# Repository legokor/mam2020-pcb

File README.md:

## Pinout

### LoRa
| Pin | ESP GPIO |
| ------ | ------ |
| MISO (2) | 19 |
| MOSI (3) | 23 |
| CLK (4) | 18 |
| CS (5)| 5 |
| RST (6)| 22 |
| DI0 (14) | 21 |

### Motors
| Pin | ESP GPIO |
| ------ | ------ |
| MOTOR_1_STEP | 27 |
| MOTOR_1_DIR | 14 |
| MOTOR_2_STEP | 12 |
| MOTOR_2_DIR | 17 |
| MOTOR_MODE_0 | 16 |
| MOTOR_MODE_1 | 4 |
| MOTOR_MODE_2 | 0 |

### ADC
| Pin | ESP GPIO |
| ------ | ------ |
| BATTERY | 34 |

### Servos
| Pin | ESP GPIO |
| ------ | ------ |
| SERVO_1 | 25 |
| SERVO_2 | 26 |

### Leds
| Pin | ESP GPIO |
| ------ | ------ |
| LED_1 | 35 |
| LED_2 | 32 |
| LED_3 | 33 |

### Connector

## Parts list

| Name | Link |
| ------ | ------ |
| ESP32 | [Pinout](https://www.rpibolt.hu/img/15922/RPI-WS16611_altpic_4/RPI-WS16611_altpic_4.jpg?time=1572739065) |
| DRV8825 | [Datasheet](https://www.pololu.com/product/2133/pictures) |
| HW-613 (DC-DC down) | [Datasheet](https://www.hestore.hu/prod_getfile.php?id=11935) |
| MT3608 (DC-DC up) | [Hestore](https://www.hestore.hu/prod_10038537.html) |
| Stepper motor ( 28BYJ ) | [Datasheet](https://www.hestore.hu/prod_getfile.php?id=8209) |
| RFM95W-868-S2 ( LoRa ) | [Datasheet](https://www.hoperf.com/data/upload/portal/20190301/RFM95_96_97_98W.pdf) |

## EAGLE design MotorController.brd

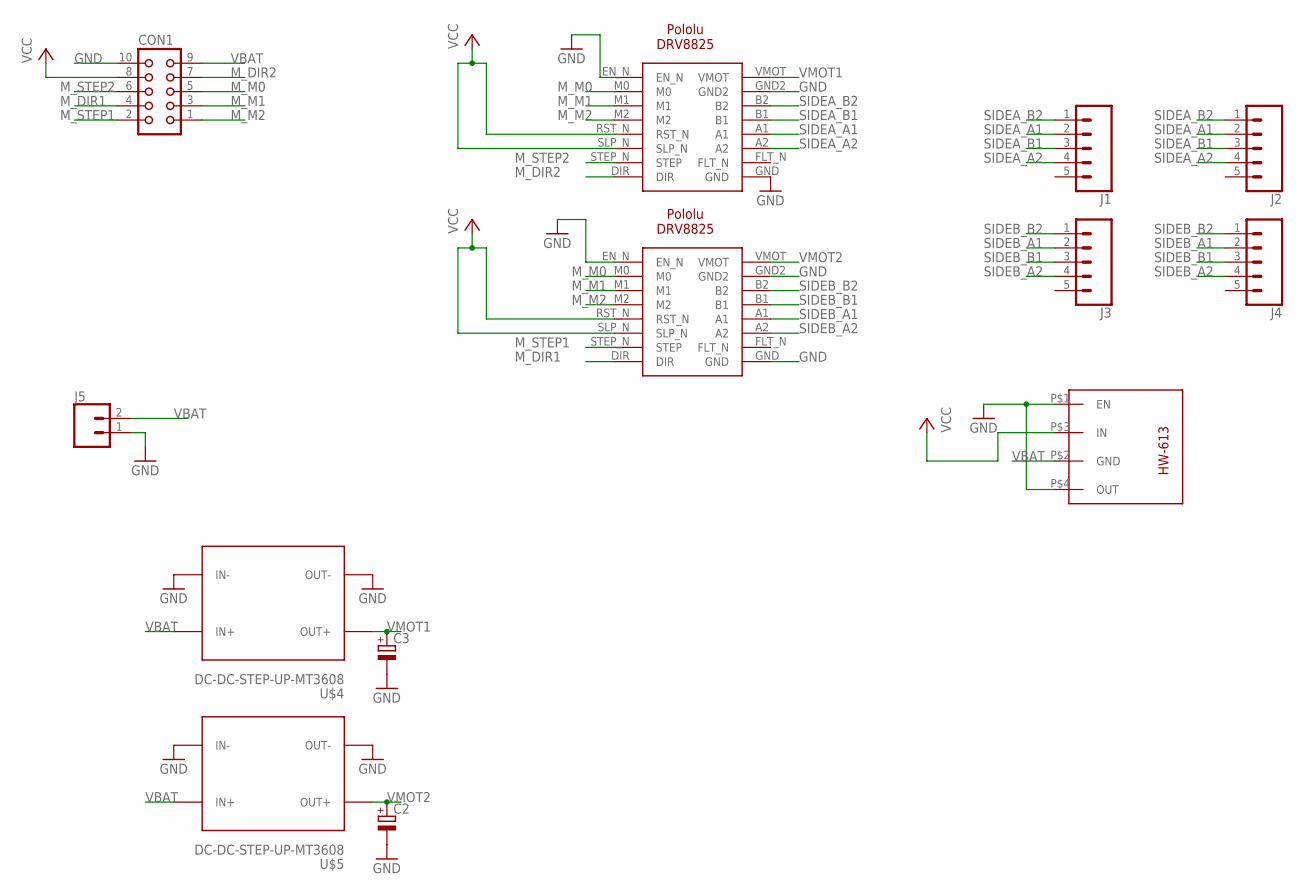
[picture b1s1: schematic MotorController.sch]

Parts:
C2, C3: CPOL-EUE3.5-10; E3,5-10
CON1: CON10
J1, J2, J3, J4: CONN_05; 1X05
J5: CONN_025MM; SCREWTERMINAL-5MM-2
U$1, U$2: POLOLU-DRV8825
U$4, U$5: DC-DC-STEP-UP-MT3608
U$6: HW-613

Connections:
GND: C2.-, C3.-, CON1.10, J5.1, U$1.EN_N, U$1.GND, U$1.GND2, U$2.EN_N, U$2.GND, U$2.GND2, U$4.IN-, U$4.OUT-, U$5.IN-, U$5.OUT-, U$6.P$1 (EN), U$6.P$4 (OUT)
M_DIR1: CON1.4, U$2.DIR
M_DIR2: CON1.7, U$1.DIR
M_M0: CON1.5, U$1.M0, U$2.M0
M_M1: CON1.3, U$1.M1, U$2.M1
M_M2: CON1.1, U$1.M2, U$2.M2
M_STEP1: CON1.2, U$2.STEP_N (STEP)
M_STEP2: CON1.6, U$1.STEP_N (STEP)
SIDEA_A1: J1.2, J2.2, U$1.A1
SIDEA_A2: J1.4, J2.4, U$1.A2
SIDEA_B1: J1.3, J2.3, U$1.B1
SIDEA_B2: J1.1, J2.1, U$1.B2
SIDEB_A1: J3.2, J4.2, U$2.A1
SIDEB_A2: J3.4, J4.4, U$2.A2
SIDEB_B1: J3.3, J4.3, U$2.B1
SIDEB_B2: J3.1, J4.1, U$2.B2
VBAT: CON1.9, J5.2, U$4.IN+, U$5.IN+, U$6.P$2 (GND)
VCC: CON1.8, U$1.RST_N, U$1.SLP_N, U$2.RST_N, U$2.SLP_N, U$6.P$3 (IN)
VMOT1: C3.+, U$1.VMOT, U$4.OUT+
VMOT2: C2.+, U$2.VMOT, U$5.OUT+

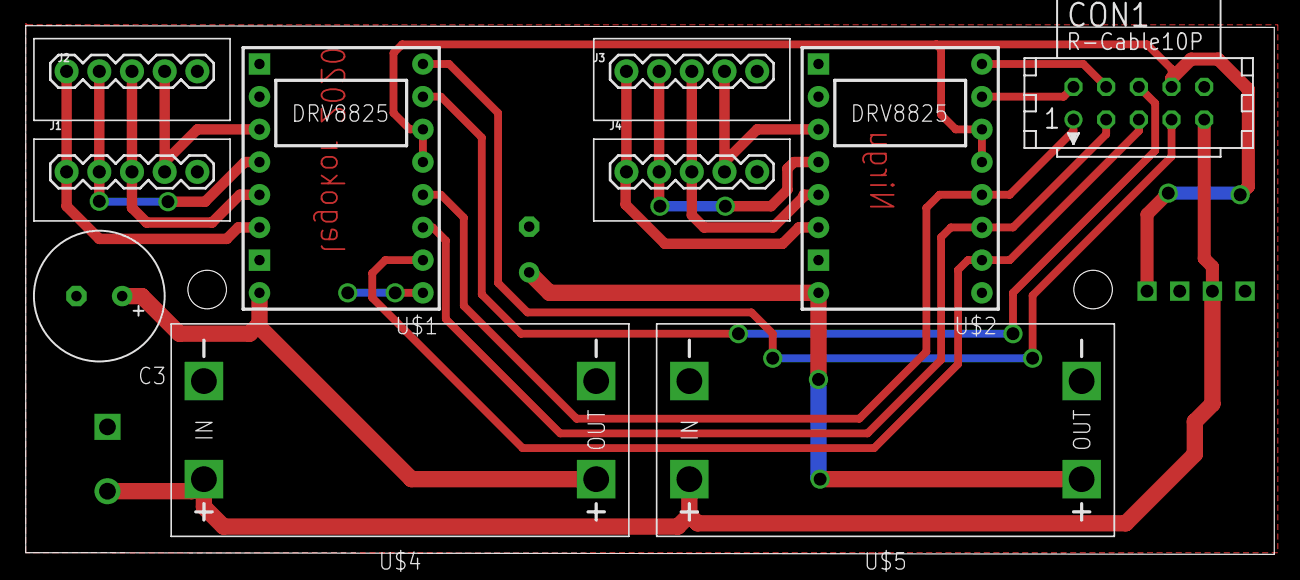
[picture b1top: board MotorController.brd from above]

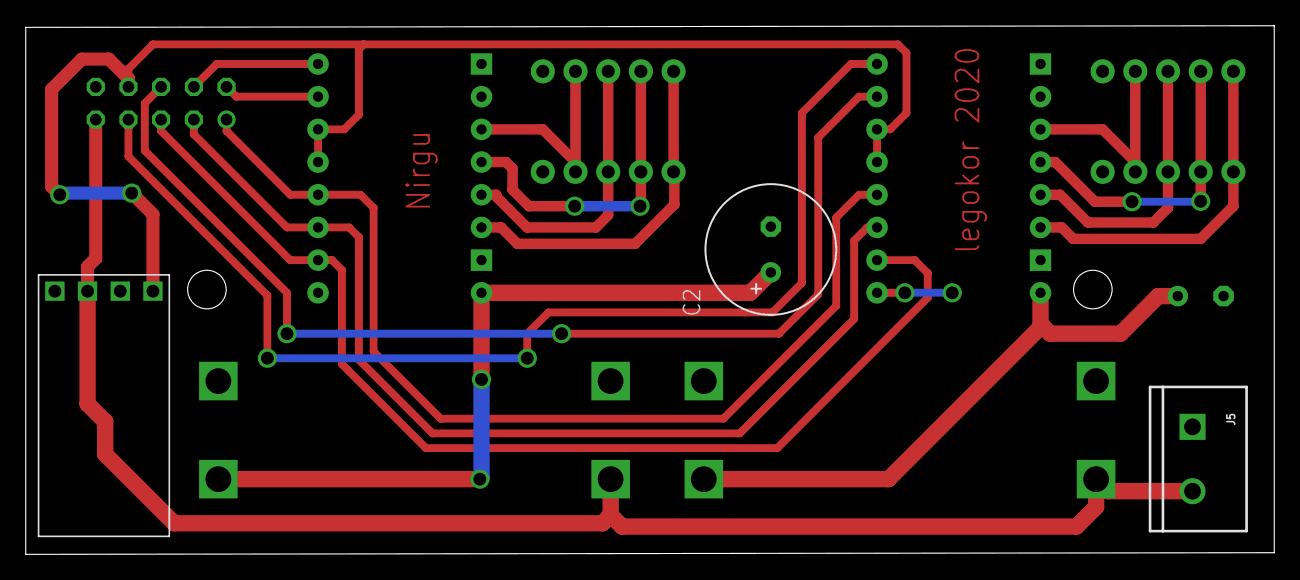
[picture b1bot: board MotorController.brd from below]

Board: 4 copper layers, 97.0 x 41.1 mm, 13 parts (3 on the bottom side), 20 nets.

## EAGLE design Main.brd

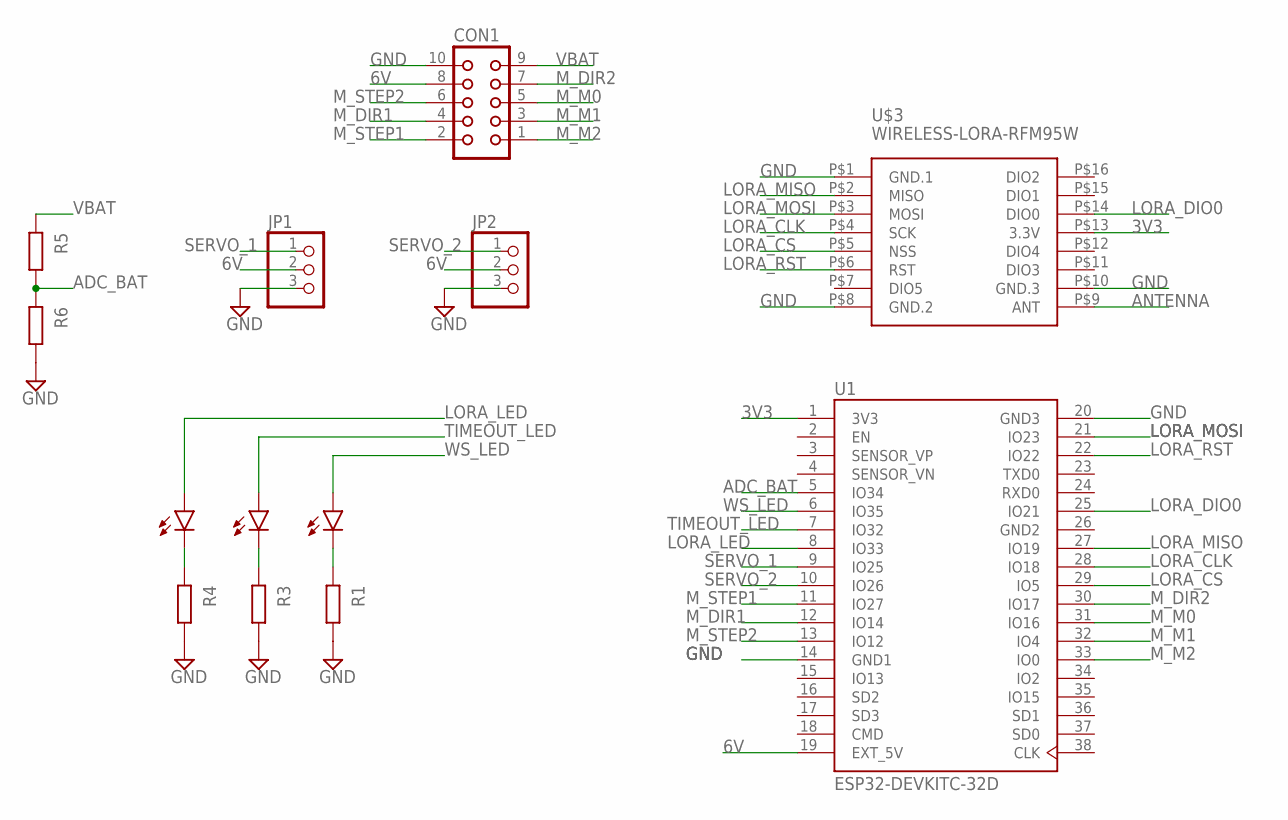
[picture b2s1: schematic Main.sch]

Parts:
CON1: CON10
JP1, JP2: PINHD-1X3; 1X03
LORA: LED_BLUE; LEDRD254W60D565H860B_B
MV: LED_BLUE; LEDRD254W60D565H860B_B
R1, R3, R4, R5, R6: R_CHIP-0603(1608-METRIC); RESC1608X60
TOUT: LED_BLUE; LEDRD254W60D565H860B_B
U1: ESP32-DEVKITC-32D; MODULE_ESP32-DEVKITC-32D
U$3: WIRELESS-LORA-RFM95W; LORA-BREAKOUT

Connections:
3V3: U1.1 (3V3), U$3.P$13 (3.3V)
6V: CON1.8, JP1.2, JP2.2, U1.19 (EXT_5V)
ADC_BAT: R5.2, R6.1, U1.5 (IO34)
ANTENNA: U$3.P$9 (ANT)
GND: CON1.10, JP1.3, JP2.3, R1.2, R3.2, R4.2, R6.2, U1.14 (GND1), U1.20 (GND3), U$3.P$1 (GND.1), U$3.P$8 (GND.2), U$3.P$10 (GND.3)
GND2: U1.26 (GND2)
LORA_CLK: U1.28 (IO18), U$3.P$4 (SCK)
LORA_CS: U1.29 (IO5), U$3.P$5 (NSS)
LORA_DIO0: U1.25 (IO21), U$3.P$14 (DIO0)
LORA_LED: MV.1 (A), U1.8 (IO33)
LORA_MISO: U1.27 (IO19), U$3.P$2 (MISO)
LORA_MOSI: U1.21 (IO23), U$3.P$3 (MOSI)
LORA_RST: U1.22 (IO22), U$3.P$6 (RST)
M_DIR1: CON1.4, U1.12 (IO14)
M_DIR2: CON1.7, U1.30 (IO17)
M_M0: CON1.5, U1.31 (IO16)
M_M1: CON1.3, U1.32 (IO4)
M_M2: CON1.1, U1.33 (IO0)
M_STEP1: CON1.2, U1.11 (IO27)
M_STEP2: CON1.6, U1.13 (IO12)
unnamed: R3.1, TOUT.2 (C)
unnamed: MV.2 (C), R4.1
unnamed: LORA.2 (C), R1.1
SERVO_1: JP1.1, U1.9 (IO25)
SERVO_2: JP2.1, U1.10 (IO26)
TIMEOUT_LED: TOUT.1 (A), U1.7 (IO32)
VBAT: CON1.9, R5.1
WS_LED: LORA.1 (A), U1.6 (IO35)

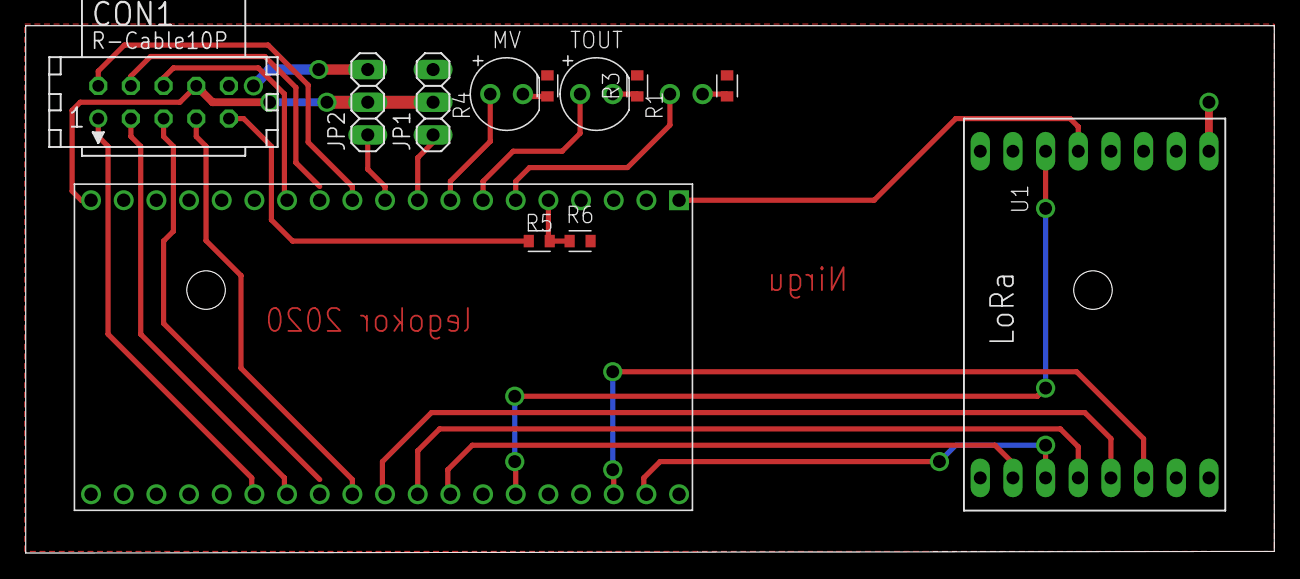
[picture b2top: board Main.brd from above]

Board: 2 copper layers, 97.1 x 41.0 mm, 13 parts (1 on the bottom side), 26 nets.

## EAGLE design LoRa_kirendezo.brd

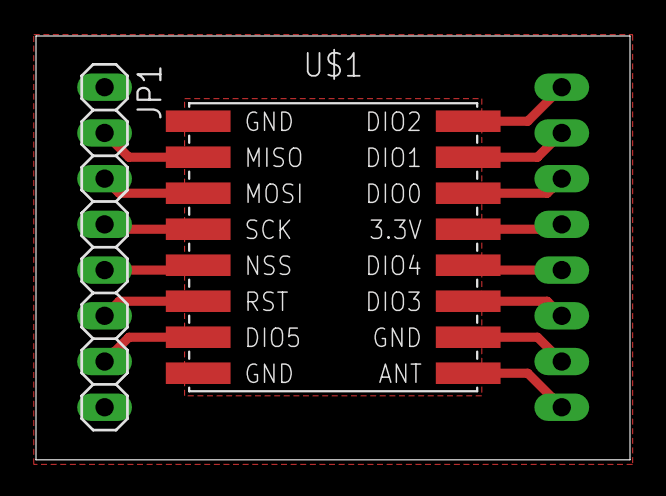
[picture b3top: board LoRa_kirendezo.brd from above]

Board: 2 copper layers, 33.0 x 23.5 mm, 3 parts (1 on the bottom side), 14 nets.

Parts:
JP1, JP2: 1X08
U$1: WIRELESS-LORA-RFM95W#SMD

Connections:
GND: JP1.1, JP1.8, JP2.7, U$1.A1, U$1.A8, U$1.B7
unnamed: JP1.2, U$1.A2
unnamed: JP1.3, U$1.A3
unnamed: JP1.4, U$1.A4
unnamed: JP1.5, U$1.A5
unnamed: JP1.6, U$1.A6
unnamed: JP1.7, U$1.A7
unnamed: JP2.8, U$1.B8
unnamed: JP2.6, U$1.B6
unnamed: JP2.5, U$1.B5
unnamed: JP2.4, U$1.B4
unnamed: JP2.3, U$1.B3
unnamed: JP2.2, U$1.B2
unnamed: JP2.1, U$1.B1

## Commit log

2020-08-25 init
2020-09-06 pcb design waiting for inspection
2020-09-06 esp32 footprint changed
2020-09-07 waiting for review
2020-09-08 fixing points added, overall pcb width modified, cable connections changed
2020-09-08 via drill size enlarged
2020-09-08 panel size fixed, fixing points added
2020-09-08 size dimensions added
2020-09-08 copyright text mirrored
2020-09-08 datasheets added to readme
2020-09-09 connector pinout added
2020-09-09 pinouts added to readme

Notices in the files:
parts and their libraries:
diy-modules: Released under the Creative Commons Attribution 4.0 International License: http://creativecommons.org/licenses/by/4.0
SparkFun-Connectors: Licensing: Creative Commons ShareAlike 4.0 International - https://creativecommons.org/licenses/by-sa/4.0
